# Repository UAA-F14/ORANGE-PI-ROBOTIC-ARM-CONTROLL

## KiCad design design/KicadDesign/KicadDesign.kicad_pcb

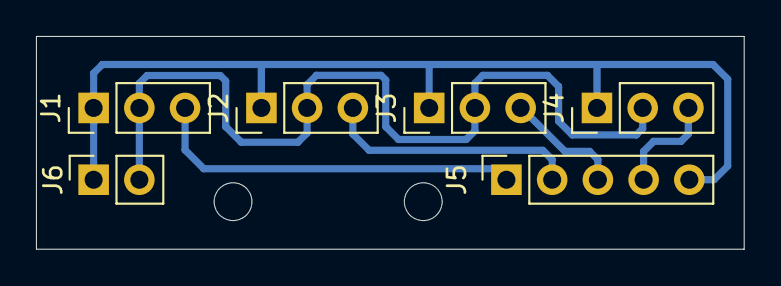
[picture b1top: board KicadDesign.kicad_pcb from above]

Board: 2 copper layers, 39.3 x 11.8 mm, 8 parts (0 on the bottom side), 6 nets.

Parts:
H1, H4: MountingHole; MountingHole_2.1mm
J1: Servo0; PinHeader_1x03_P2.54mm_Vertical
J2: Servo1; PinHeader_1x03_P2.54mm_Vertical
J3: Servo2; PinHeader_1x03_P2.54mm_Vertical
J4: Servo3; PinHeader_1x03_P2.54mm_Vertical
J5: ORANGE; PinSocket_1x05_P2.54mm_Vertical
J6: Source; PinSocket_1x02_P2.54mm_Vertical

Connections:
/PWM0: J1.3, J5.1
/PWM1: J2.3, J5.2
/PWM2: J3.3, J5.3
/PWM3: J4.3, J5.4
GND: J1.1, J2.1, J3.1, J4.1, J5.5, J6.1
VCC: J1.2, J2.2, J3.2, J4.2, J6.2
